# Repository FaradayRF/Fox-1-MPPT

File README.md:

# Fox-1-MPPT
This repository contains the Public Domain files of the [Radio Amateur Satellite Corporation](http://www.amsat.org) (AMSAT) Fox-1 satellite Maximum Power Point Tracker. This is a PCBA flying on the Fox-1 series of 1U cubesats which optimizes the power extracted from the six solar panels on the spacecraft using analog computing.

# Overview

The Fox-1 Maximum Power Point Tracker utilizes analog computing to track the solar panel voltage which generates the maximum amount of power from solar cells. It implements what is essentially a "temperature-based set-point constant voltage algorithm" MPPT. Since the solar cells are well-known, this design uses op-amps to compute the predicted voltage which will produce maximum power as fast as the analog bandwidth of the components used will allow it. Analog MPPT was chosen for it's "stateless" design due to radiation tolerance concerns of microcontrollers.

Revision 1.2 boards are Revision 1 PCB's with BOM modifications necessary for correct operation. This included stacking some capacitors ontop of feedback resistors in the RTD circuit for stability. Revision 1 PCB's are green soldermask in color. Revision 2 PCB's were created to adress these issues better and properly mount all parts with correct footprints and adress some other manufacturing needs. These boards are use a blue soldermask and the design files for the Rev 2.1 boards have been uploaded to this Github repository.

[READ THE FOX-1 MPPT TECHNICAL OVERVIEW TO UNDERSTAND THE PROJECT!](https://github.com/FaradayRF/Fox-1-MPPT/blob/master/Documents/Fox-1_MaximumPowerPointTracker.pdf)

# History
This project began as a [Rochester Institute of Technology](https://www.rit.edu/) Multi-disciplinary Senior Design (MSD) project during the 2012-2013 school year. Originally the [P13271 AMSAT-MPPT](http://edge.rit.edu/edge/P13271/public/Home) project which successfully delivered a proof-of-concept MPPT intended for a 3U cubesat, the design was continued and modified for use on the smaller Fox-1 satellites which are 1U in size.

## Original Team
The original RIT team to create this MPPT included
* Bryce Salmi, KB1LQC
* Brenton Salmi, KB1LQD
* Ian MacKenzi, KB3OCF
* Daniel Corriero

Work was performed over two years between 2013 and 2015 by Bryce Salmi and Brenton Salmi to bring the design to flight status from the P13271 project as seen here.

# Flights
The Revision 1.2 and Revision 2.1 Maximum Power Point Trackers are currently slated to fly on several launches to Low Earth Orbit with more launches being sought after. These flights are accurate as of 9/3/2016.

### Fox-1Cliff and Fox-1D
Two MPPTs will fly aboard two cubesats on the same launch. These satellites are Fox-1Cliff and Fox-1D which are being sent up on the Spaceflight SHERPA payload on a [SpaceX Falcon 9](http://www.spacex.com/falcon9).

### Fox-1B "RadFxSat"
One MPPT will be flying on the Fox-1B cubesat set to launch aboard a ULA [Delta II](http://www.ulalaunch.com/Products_DeltaII.aspx) rocket.

### Fox-1E "RadFxSat-2"
One MPPT will be flying on the Fox-1E cubesat set to launch aboard a [Virgin Galactic Launcher One](http://www.virgingalactic.com/satellite-launch/) in December, 2017.

# Project Structure
## Hardware Files
All hardware files are located in the [Hardware/Rev2_1](https://github.com/FaradayRF/Fox-1-MPPT/tree/master/Hardware/Rev2_1) directory. They consist of [Kicad EDA](http://kicad.org/) files which were developed using [Kicad Build: 2013-07-07 BZR 4022]https://downloads.kicad.org/kicad/windows/explore/stable) which is the July 2013 stable version of the EDA tool (Windows). Also placed into the hardware directory are the [project output files](https://github.com/FaradayRF/Fox-1-MPPT/tree/master/Hardware/Rev2_1/OutputFiles). These are the files which were used to order the PCBs and present an easy to use view of the design (PDF, Excel, Gerber, etc).

**Notable Documents**
* [MPPT Schematic PDF Export](https://github.com/FaradayRF/Fox-1-MPPT/blob/master/Hardware/Rev2_1/OutputFiles/TL1451_MPPT_Flight_Rev2_BW.pdf)
* [MPPT BOM](https://github.com/FaradayRF/Fox-1-MPPT/blob/master/Hardware/Rev2_1/OutputFiles/TL1451_MPPT_Flight_Rev2_BOM.xlsx)
* [MPPT Extra Components BOM](https://github.com/FaradayRF/Fox-1-MPPT/blob/master/Hardware/Rev2_1/OutputFiles/TL1451_MPPT_Flight_Rev2_Additional_BOM.xlsx)
 * Addition parts for the solar panels necessary for the MPPT to work
* [MPPT KiCad project file](https://github.com/FaradayRF/Fox-1-MPPT/blob/master/Hardware/Rev2_1/TL1451_MPPT_Flight_Rev1.pro)
* [KB1LQC KiCad schematic symbol library](https://github.com/FaradayRF/Fox-1-MPPT/blob/master/Hardware/Rev2_1/KB1LQC.lib)
* [KB1LQC KiCad PCBNew footprint library](https://github.com/FaradayRF/Fox-1-MPPT/blob/master/Hardware/Rev2_1/KB1LQC.mod)
* [MPPT PCB Fabrication Files](https://github.com/FaradayRF/Fox-1-MPPT/blob/master/Hardware/Rev2_1/OutputFiles/TL1451_MPPT_Flight_Rev2_1_FAB_Files.zip)
* [MPPT PCBA Assembly Files](https://github.com/FaradayRF/Fox-1-MPPT/blob/master/Hardware/Rev2_1/OutputFiles/TL1451_MPPT_Flight_Rev2_1_ASSEMBLY_Files.zip)

## Documents
The [documents folder](https://github.com/FaradayRF/Fox-1-MPPT/tree/master/Documents) contains support documents necessary to describe the design intentions and analysis of the MPPT.

**Notable Documents**
* [Fox-1 MPPT Technical Overview](https://github.com/FaradayRF/Fox-1-MPPT/blob/master/Documents/Fox-1_MaximumPowerPointTracker.pdf)
* [Fox-1 Satellite Solar Panel Calculations](https://github.com/FaradayRF/Fox-1-MPPT/blob/master/Documents/MPPT_Expected_Voltages_Fox-1.xlsx)
* [Fox-1 Solar Panel Telemetry Scaling](https://github.com/FaradayRF/Fox-1-MPPT/blob/master/Documents/PanelTemperatureScaling.xlsx)
 * Scaling telemetry downlinked from satellite over RF into Celcius from RTD circuit

## Images
The [images directory](https://github.com/FaradayRF/Fox-1-MPPT/tree/master/images) contains a select set of high-quality stock images showing the Rev 2 MPPT very clearly. Not much more needed to say about this :rocket:

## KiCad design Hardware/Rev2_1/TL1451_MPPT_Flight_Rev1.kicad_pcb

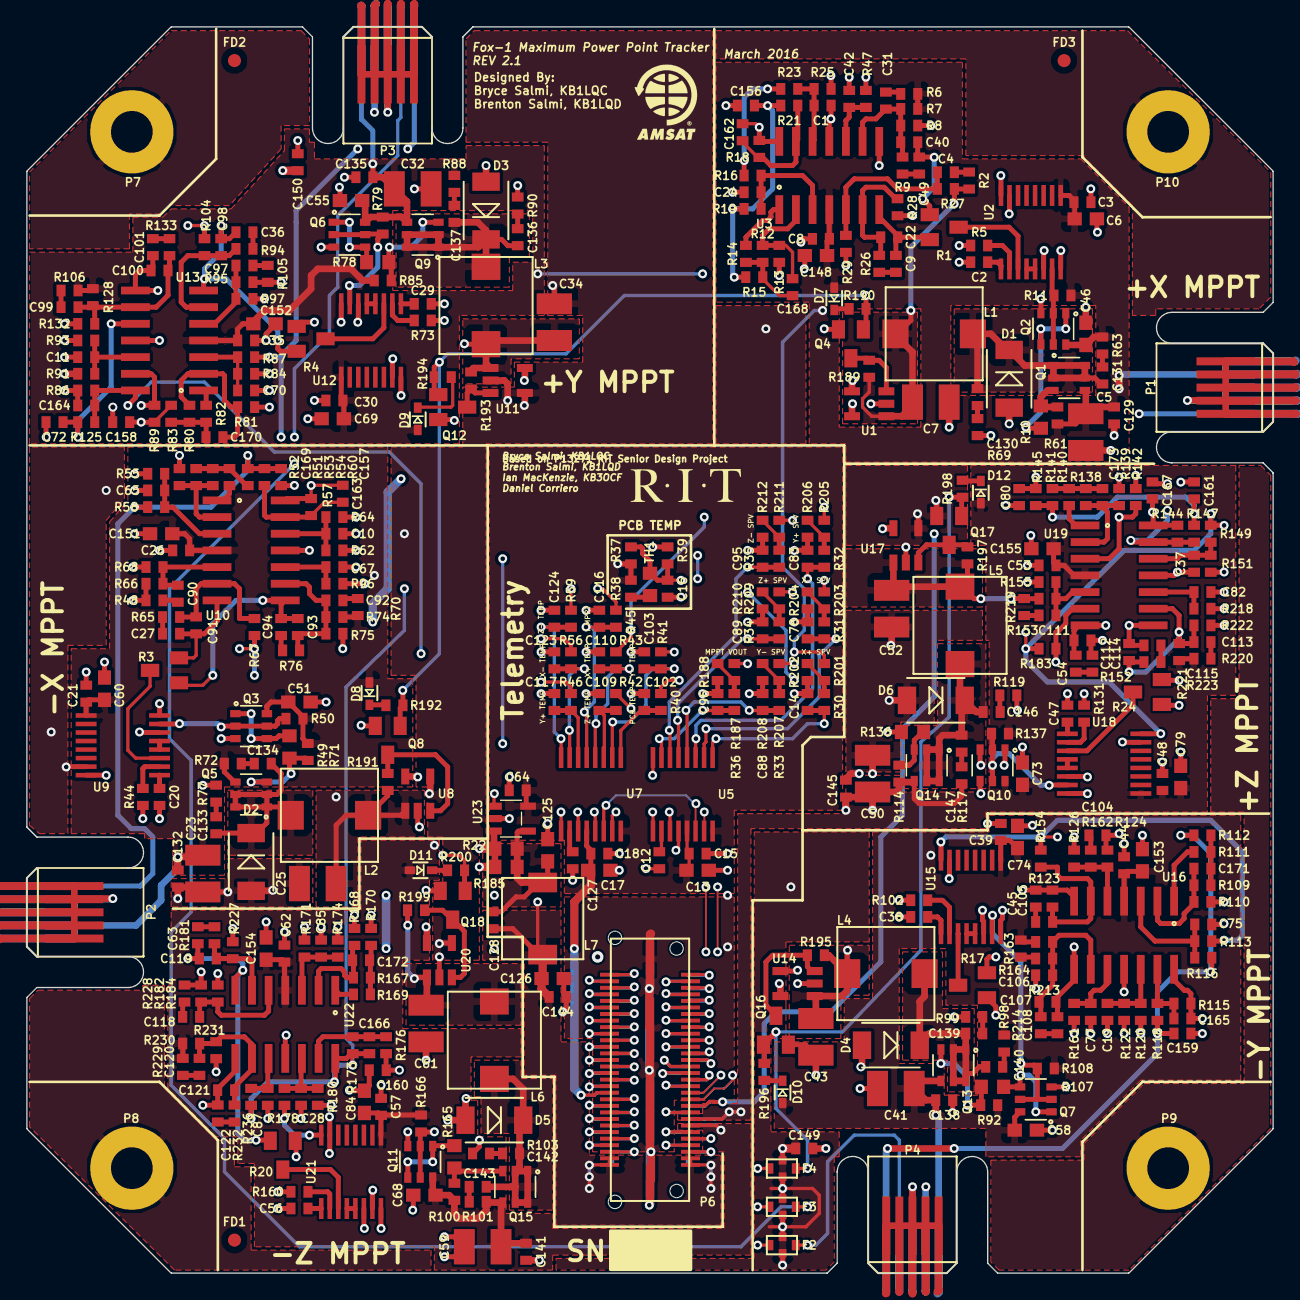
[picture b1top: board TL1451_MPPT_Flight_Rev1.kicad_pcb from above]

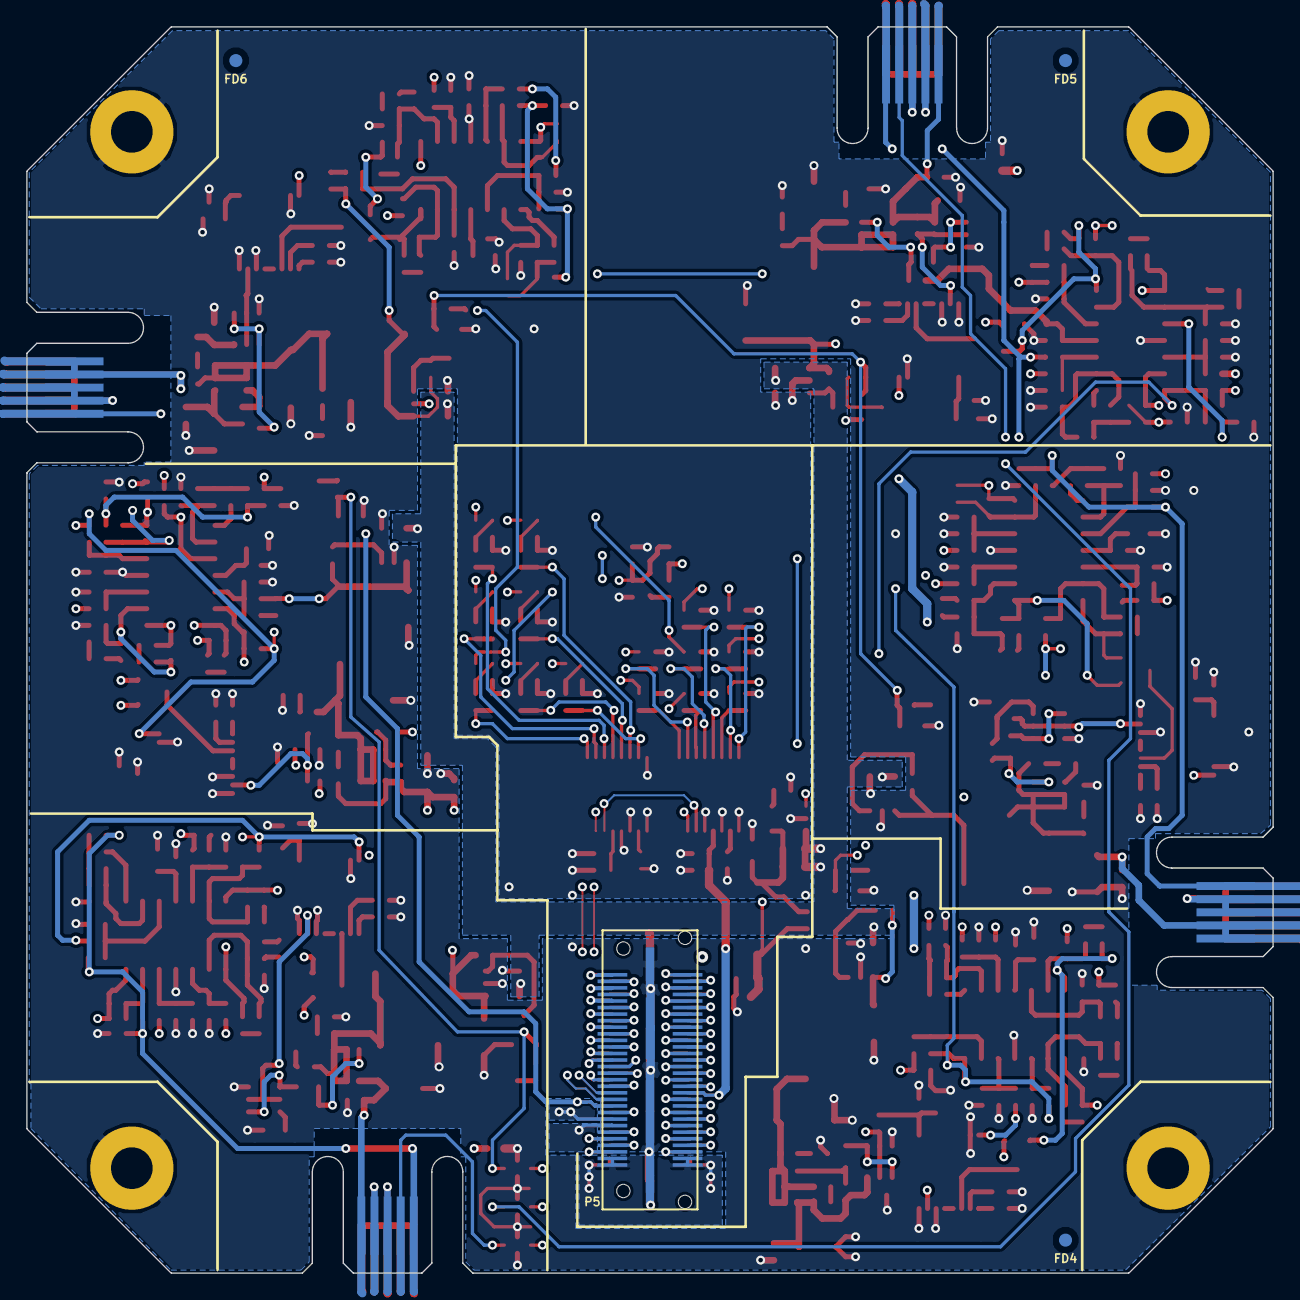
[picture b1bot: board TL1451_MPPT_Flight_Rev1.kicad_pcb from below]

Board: 4 copper layers, 95.0 x 95.0 mm, 455 parts (4 on the bottom side), 284 nets.

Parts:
C1, C3, C8, C10, C11, C15, C16, C18, C19, C21, C24, C26, C28, C30, C35, C37, C39, C44, C48, C53, C57, C62, C64, C65, C70, C75, C80, C85, C129, C132, C135, C138, C141, C144, C145, C149, C150, C156, C157, C158, C159, C160, C161, C162, C163, C164, C165, C166, C167, C168, C169, C170, C171, C172, C173: 0.1uF; C0402
C2, C20, C29, C38, C47, C56: 220pF; C0402
C4, C31, C90, C92, C97, C99, C104, C106, C111, C113, C118, C120: 0.012uF; C0402
C5, C7, C23, C25, C32, C34, C41, C43, C50, C52, C59, C61: 47uF; C1210
C6, C13, C17, C46, C51, C55, C58, C60, C68, C69, C73, C74, C79, C84, C148, C151, C152, C153, C154, C155: 1uF; C0603
C9, C27, C36, C45, C49, C54, C63, C94, C101, C108, C115, C122: 0.015uF; C0402
C12, C14, C42, C67, C72, C77, C78, C82, C83, C87, C88, C89, C95, C96, C102, C103, C109, C110, C116, C117, C123, C124, C127: 1uF; C0402
C22, C40, C91, C93, C98, C100, C105, C107, C112, C114, C119, C121: 820pF; C0402
C125, C126: 0.39uF; C0603
C128: 0.01uF; C0402
C130, C131, C133, C134, C136, C137, C139, C140, C142, C143, C146, C147: DNP; C0402
D1, D2, D3, D4, D5, D6: PMEG3020EP; SOD128
D7, D8, D9, D10, D11, D12: SDM10U45-7; SOD523
F2, F3, F4: NFL21SP106X1C3D; NFL21SP
FD1, FD2, FD3, FD4, FD5, FD6: FIDUCIAL; FD1
G1: AMSAT_LOGO_SMALL; AMSAT_Logo_Small
G2: RIT_LOGO_SMALL; RIT_Logo_Small
L1, L2, L3, L4, L5, L6: 22uH; CLF7045T
L7: 10uH; SLF6045
P1, P2, P3, P4: CONN_5X2; MEC1-105-02-L-D-NP-A
P5: QSH-030-01-X-D-A; QSH-030-01-L-D-A
P6: QTH-030-02-X-D-A; QTH-030-02-L-D-A
P7, P8, P9, P10: CONN_1; FOX_Mounting_Hole
Q1, Q5, Q9, Q13, Q14, Q15: DMP2066LDM-7; SOT26
Q2, Q3, Q6, Q7, Q10, Q11: MMDT2227M; SOT26
Q4, Q8, Q12, Q16, Q17, Q18: 2N7002K; SOT23
R1, R3, R4, R17, R20, R24: MPMT4001AT1; SOT23
R2, R6, R48, R70, R105, R106, R162, R163, R219, R220, R228, R229: 261; R0402
R5, R44, R73, R102, R131, R160: 4.99K; R0402
R7, R27, R66, R74, R95, R124, R128, R153, R164, R182, R221, R230: 4.75K; R0402
R8, R75, R132, R213, R222, R231: 1.54K; R0402
R9, R21, R26, R60, R65, R76, R89, R94, R118, R123, R133, R147, R152, R176, R181, R214, R223, R232: 3.32K; R0402
R10, R49, R78, R107, R136, R165: 6.04; R0603
R11, R50, R79, R108, R137, R166: 2K; R0402
R12, R13, R16, R19, R51, R52, R55, R58, R80, R81, R84, R87, R109, R110, R113, R116, R138, R139, R142, R145, R167, R168, R171, R174: 249K; R0402
R14, R53, R82, R111, R140, R169: 100; R0402
R15, R54, R83, R112, R141, R170: 2.49K; R0402
R18, R57, R86, R115, R144, R173: 27K; R0402
R22, R185: 0.051; R0603
R23, R62, R91, R120, R149, R178: 24.3K; R0402
R25, R64, R93, R122, R151, R180: 2.4K; R0402
R28, R30, R31, R32, R33, R34, R35, R36, R40, R41, R42, R43, R45, R46, R56, R59, R67, R104, R154, R183, R189, R190, R191, R192, R193, R194, R195, R196, R197, R198, R199, R200, R227: 10K; R0402
R29, R68, R97, R126, R155, R184: 6.49K; R0402
R37: 71.5K; R0402
R38: 330; R0402
R39: 9.09K; R0402
R47, R96, R125, R161, R218, R236: 47K; R0402
R61, R71, R85, R92, R100, R114: 205K; R0402
R63, R69, R72, R77, R88, R90, R98, R99, R101, R103, R117, R119: DNP; R0402
R187, R202, R204, R206, R208, R210, R212: 30.1K; R0402
R188: 40.2K; R0402
R201, R203, R205, R207, R209, R211: 51.1K; R0402
TH1: NTCS0603E3103FMT; R0603
U1, U8, U11, U14, U17, U20: LTC4411; TSOT23-5
U2, U9, U12, U15, U18, U21: TL1451A; PW16
U3, U10, U13, U16, U19, U22: LM6144A; SO14
U5, U7: ADS7828; PW16
U23: INA195; SOT23-5

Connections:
/ADC Channels/Temperature & Current ADC/I2C_SCL: P5.37, P6.37, U5.14, U7.14
/ADC Channels/Temperature & Current ADC/I2C_SDA: P5.39, P6.39, U5.15, U7.15
/ADC Channels/Temperature & Current ADC/MPPT-OUTPUT-CURRENT: R45.1, U23.1
/ADC Channels/Temperature & Current ADC/SENSOR_POWER: C13.1, C15.1, C17.1, C18.1, C64.1, P5.38, P6.38, R37.1, R38.1, U5.13, U5.16, U7.12, U7.16, U23.5
/ADC Channels/Voltage Sense ADC/VMPPT: R36.1, R187.2, R188.1
/BUS44: C149.1, P4.8, P5.44, P6.44
/BUS46: F2.3, P4.4
/BUS48: F3.3, P3.4
/BUS50: C150.1, P3.8, P5.50, P6.50
/Connectors/BUS1: P5.1, P6.1
/Connectors/BUS2: P5.2, P6.2
/Connectors/BUS3: P5.3, P6.3
/Connectors/BUS4: P5.4, P6.4
/Connectors/BUS5: P5.5, P6.5
/Connectors/BUS6: P5.6, P6.6
/Connectors/BUS7: P5.7, P6.7
/Connectors/BUS8: P5.8, P6.8
/Connectors/BUS9: P5.9, P6.9
/Connectors/BUS10: P5.10, P6.10
/Connectors/BUS11: P5.11, P6.11
/Connectors/BUS12: P5.12, P6.12
/Connectors/BUS13: P5.13, P6.13
/Connectors/BUS14: P5.14, P6.14
/Connectors/BUS15: P5.15, P6.15
/Connectors/BUS16: P5.16, P6.16
/Connectors/BUS17: P5.17, P6.17
/Connectors/BUS18: P5.18, P6.18
/Connectors/BUS19: P5.19, P6.19
/Connectors/BUS20: P5.20, P6.20
/Connectors/BUS21: P5.21, P6.21
/Connectors/BUS22: P5.22, P6.22
/Connectors/BUS23: P5.23, P6.23
/Connectors/BUS24: P5.24, P6.24
/Connectors/BUS25: P5.25, P6.25
/Connectors/BUS26: P5.26, P6.26
/Connectors/BUS27: P5.27, P6.27
/Connectors/BUS28: P5.28, P6.28
/Connectors/BUS29-UNF: F4.1, P5.29, P6.29
/Connectors/BUS30: P5.30, P6.30
/Connectors/BUS31: P5.31, P6.31
/Connectors/BUS32: P5.32, P6.32
/Connectors/BUS33: P5.33, P6.33
/Connectors/BUS34: P5.34, P6.34
/Connectors/BUS35: P5.35, P6.35
/Connectors/BUS36: P5.36, P6.36
/Connectors/BUS40: P5.40, P6.40
/Connectors/BUS42: P5.42, P6.42
/Connectors/BUS46-UNF: F2.1, P5.46, P6.46
/Connectors/BUS48-UNF: F3.1, P5.48, P6.48
/Connectors/BUS49: P5.49, P6.49
/Connectors/BUS51: P5.51, P6.51
/Connectors/BUS52: P5.52, P6.52
/Connectors/BUS53: P5.53, P6.53
/Connectors/BUS54: P5.54, P6.54
/Connectors/BUS55: P5.55, P6.55
/Connectors/BUS56: P5.56, P6.56
/Current Sense/I_SENSE+: R22.1, R185.1, U1.5, U8.5, U11.5, U14.5, U17.5, U20.5, U23.3
/Current Sense/Sense-: C125.1, C128.1, L7.1, R22.2, R185.2, U23.4
/Current Sense/VBATT: C126.1, C128.2, C144.1, L7.2, P5.57, P5.58, P5.59, P5.60, P6.57, P6.58, P6.59, P6.60, R187.1
/MPPT_String_X+/Amplifiers/VREF: R16.1, R23.1, R28.1, U2.16
/MPPT_String_X+/Amplifiers/Verror: R1.3, U2.3
/MPPT_String_X+/RTD+: C156.2, P1.2, R15.2, R19.2, R21.1
/MPPT_String_X+/TL1451 Control/MOSFET Driver/GATE-DRIVE: Q2.1, Q2.4, R10.1
/MPPT_String_X+/TL1451 Control/MOSFET Driver/PWM-IN: Q2.2, Q2.5, R11.2, U2.7
/MPPT_String_X+/TL1451 Control/MPPT-OUT: C7.1, L1.2, R2.1, R27.1, R189.1, U1.1
/MPPT_String_X+/TL1451 Control/Non-Synchronouse_BUCK/Vswitch: C130.1, C131.2, D1.1, L1.1, Q1.1, Q1.2, Q1.5, Q1.6
/MPPT_String_X+/Vpanel+: C3.1, C5.1, C6.1, C8.1, C46.1, C129.1, C148.1, D7.2, P1.8, P1.10, Q1.4, Q2.6, R6.1, R7.1, R11.1, R61.1, R63.1, R201.1, U2.9, U3.4
/MPPT_String_X+/Vtemp: C162.1, R18.2, R43.1, R47.1, U3.14
/MPPT_String_X+/~SolarSafe~: F4.3, Q4.1, Q8.1, Q12.1, Q16.1, Q17.1, Q18.1, R190.2, R192.2, R194.2, R196.2, R198.2, R200.2
/MPPT_String_X-/Amplifiers/VREF: R55.1, R62.1, R67.1, U9.16
/MPPT_String_X-/Amplifiers/Verror: R3.3, U9.3
/MPPT_String_X-/RTD+: C157.2, P2.2, R54.2, R58.2, R60.1
/MPPT_String_X-/TL1451 Control/MOSFET Driver/GATE-DRIVE: Q3.1, Q3.4, R49.1
/MPPT_String_X-/TL1451 Control/MOSFET Driver/PWM-IN: Q3.2, Q3.5, R50.2, U9.7
/MPPT_String_X-/TL1451 Control/MPPT-OUT: C25.1, L2.2, R48.1, R66.1, R191.1, U8.1
/MPPT_String_X-/TL1451 Control/Non-Synchronouse_BUCK/Vswitch: C133.1, C134.2, D2.1, L2.1, Q5.1, Q5.2, Q5.5, Q5.6
/MPPT_String_X-/Vpanel+: C21.1, C23.1, C26.1, C51.1, C60.1, C132.1, C151.1, D8.2, P2.8, P2.10, Q3.6, Q5.4, R50.1, R70.1, R71.1, R72.1, R74.1, R203.1, U9.9, U10.4
/MPPT_String_X-/Vtemp: C163.1, R56.1, R57.2, R96.1, U10.14
/MPPT_String_Y+/Amplifiers/VREF: R84.1, R91.1, R104.1, U12.16
/MPPT_String_Y+/Amplifiers/Verror: R4.3, U12.3
/MPPT_String_Y+/RTD+: C158.2, P3.2, R83.2, R87.2, R89.1
/MPPT_String_Y+/TL1451 Control/MOSFET Driver/GATE-DRIVE: Q6.1, Q6.4, R78.1
/MPPT_String_Y+/TL1451 Control/MOSFET Driver/PWM-IN: Q6.2, Q6.5, R79.2, U12.7
/MPPT_String_Y+/TL1451 Control/MPPT-OUT: C34.1, L3.2, R95.1, R105.1, R193.1, U11.1
/MPPT_String_Y+/TL1451 Control/Non-Synchronouse_BUCK/Vswitch: C136.1, C137.2, D3.1, L3.1, Q9.1, Q9.2, Q9.5, Q9.6
/MPPT_String_Y+/Vpanel+: C30.1, C32.1, C35.1, C55.1, C69.1, C135.1, C152.1, D9.2, P3.10, Q6.6, Q9.4, R79.1, R85.1, R88.1, R106.1, R128.1, R205.1, U12.9, U13.4
/MPPT_String_Y+/Vtemp: C164.1, R46.1, R86.2, R125.1, U13.14
/MPPT_String_Y-/Amplifiers/VREF: R113.1, R120.1, R154.1, U15.16
/MPPT_String_Y-/Amplifiers/Verror: R17.3, U15.3
/MPPT_String_Y-/RTD+: C159.2, P4.2, R112.2, R116.2, R118.1
/MPPT_String_Y-/TL1451 Control/MOSFET Driver/GATE-DRIVE: Q7.1, Q7.4, R107.1
/MPPT_String_Y-/TL1451 Control/MOSFET Driver/PWM-IN: Q7.2, Q7.5, R108.2, U15.7
/MPPT_String_Y-/TL1451 Control/MPPT-OUT: C43.1, L4.2, R124.1, R162.1, R195.1, U14.1
/MPPT_String_Y-/TL1451 Control/Non-Synchronouse_BUCK/Vswitch: C139.1, C140.2, D4.1, L4.1, Q13.1, Q13.2, Q13.5, Q13.6
/MPPT_String_Y-/Vpanel+: C39.1, C41.1, C44.1, C58.1, C74.1, C138.1, C153.1, D10.2, P4.10, Q7.6, Q13.4, R92.1, R98.1, R108.1, R163.1, R164.1, R207.1, U15.9, U16.4
/MPPT_String_Y-/Vtemp: C165.1, R41.1, R115.2, R161.1, U16.14
/MPPT_String_Z+/Amplifiers/VREF: R142.1, R149.1, R183.1, U18.16
/MPPT_String_Z+/Amplifiers/Verror: R24.3, U18.3
/MPPT_String_Z+/RTD+: C161.2, P5.41, P6.41, R141.2, R145.2, R147.1
/MPPT_String_Z+/TL1451 Control/MOSFET Driver/GATE-DRIVE: Q10.1, Q10.4, R136.1
/MPPT_String_Z+/TL1451 Control/MOSFET Driver/PWM-IN: Q10.2, Q10.5, R137.2, U18.7
/MPPT_String_Z+/TL1451 Control/MPPT-OUT: C52.1, L5.2, R153.1, R197.1, R219.1, U17.1
/MPPT_String_Z+/TL1451 Control/Non-Synchronouse_BUCK/Vswitch: C146.1, C147.2, D6.1, L5.1, Q14.1, Q14.2, Q14.5, Q14.6
/MPPT_String_Z+/Vpanel+: C48.1, C50.1, C53.1, C73.1, C79.1, C145.1, C155.1, D12.2, P5.45, P6.45, Q10.6, Q14.4, R114.1, R117.1, R137.1, R209.1, R220.1, R221.1, U18.9, U19.4
/MPPT_String_Z+/Vtemp: C167.1, R42.1, R144.2, R218.1, U19.14
/MPPT_String_Z-/Amplifiers/VREF: R171.1, R178.1, R227.1, U21.16
/MPPT_String_Z-/Amplifiers/Verror: R20.3, U21.3
/MPPT_String_Z-/RTD+: C160.2, P5.43, P6.43, R170.2, R174.2, R176.1
/MPPT_String_Z-/TL1451 Control/MOSFET Driver/GATE-DRIVE: Q11.1, Q11.4, R165.1
/MPPT_String_Z-/TL1451 Control/MOSFET Driver/PWM-IN: Q11.2, Q11.5, R166.2, U21.7
/MPPT_String_Z-/TL1451 Control/MPPT-OUT: C61.1, L6.2, R182.1, R199.1, R228.1, U20.1
/MPPT_String_Z-/TL1451 Control/Non-Synchronouse_BUCK/Vswitch: C142.1, C143.2, D5.1, L6.1, Q15.1, Q15.2, Q15.5, Q15.6
/MPPT_String_Z-/Vpanel+: C57.1, C59.1, C62.1, C68.1, C84.1, C141.1, C154.1, D11.2, P5.47, P6.47, Q11.6, Q15.4, R100.1, R101.1, R166.1, R211.1, R229.1, R230.1, U21.9, U22.4
/MPPT_String_Z-/Vtemp: C166.1, R59.1, R173.2, R236.1, U22.14
/Panel Voltage Scaling/Vsense+X: R30.1, R201.2, R202.1
/Panel Voltage Scaling/Vsense+Y: R32.1, R205.2, R206.1
/Panel Voltage Scaling/Vsense+Z: R34.1, R209.2, R210.1
/Panel Voltage Scaling/Vsense-X: R31.1, R203.2, R204.1
/Panel Voltage Scaling/Vsense-Y: R33.1, R207.2, R208.1
/Panel Voltage Scaling/Vsense-Z: R35.1, R211.2, R212.1
GND: C1.1, C2.2, C3.2, C5.2, C6.2, C7.2, C8.2, C10.1, C11.1, C12.2, C13.2, C14.2, C15.2, C16.2, C17.2, C18.2, C19.1, C20.2, C21.2, C23.2, C24.1, C25.2, C26.2, C28.1, C29.2, C30.2, C32.2, C34.2, C35.2, C37.1, C38.2, C39.2, C41.2, C42.1, C43.2, C44.2, C46.2, C47.2, C48.2, C50.2, C51.2, C52.2, C53.2, C55.2, C56.2, C57.2, C58.2, C59.2, C60.2, C61.2, C62.2, C64.2, C65.1, C67.1, C68.2, C69.2, C70.1, C72.1, C73.2, C74.2, C75.1, C77.1, C78.2, C79.2, C80.1, C82.1, C83.2, C84.2, C85.1, C87.1, C88.2, C89.2, C95.2, C96.2, C102.2, C103.2, C109.2, C110.2, C116.2, C117.2, C123.2, C124.2, C125.2, C126.2, C127.2, C129.2, C132.2, C135.2, C138.2, C141.2, C144.2, C145.2, C148.2, C149.2, C150.2, C151.2, C152.2, C153.2, C154.2, C155.2, C156.1, C157.1, C158.1, C159.1, C160.1, C161.1, D1.2, D2.2, D3.2, D4.2, D5.2, D6.2, F2.2, F3.2, F4.2, P1.1, P1.3, P1.4, P1.5, P1.6, P1.7, P1.9, P2.1, P2.3, P2.4, P2.5, P2.6, P2.7, P2.9, P3.1, P3.3, P3.5, P3.6, P3.7, P3.9, P4.1, P4.3, P4.5, P4.6, P4.7, P4.9, P5.61, P5.62, P5.63, P5.64, P6.61, P6.62, P6.63, P6.64, P7.1, P8.1, P9.1, P10.1, Q2.3, Q3.3, Q4.2, Q6.3, Q7.3, Q8.2, Q10.3, Q11.3, Q12.2, Q16.2, Q17.2, Q18.2, R5.2, R8.2, R13.1, R25.2, R29.2, R39.2, R44.2, R52.1, R64.2, R68.2, R69.2, R73.2, R75.2, R77.2, R81.1, R90.2, R93.2, R97.2, R99.2, R102.2, R103.2, R110.1, R119.2, R122.2, R126.2, R131.2, R132.2, R139.1, R151.2, R155.2, R160.2, R168.1, R180.2, R184.2, R188.2, R202.2, R204.2, R206.2, R208.2, R210.2, R212.2, R213.2, R222.2, R231.2, U1.2, U1.4, U2.6, U2.8, U2.15, U3.11, U5.8, U5.9, U5.11, U5.12, U7.9, U7.11, U7.13, U8.2, U8.4, U9.6, U9.8, U9.15, U10.11, U11.2, U11.4, U12.6, U12.8, U12.15, U13.11, U14.2, U14.4, U15.6, U15.8, U15.15, U16.11, U17.2, U17.4, U18.6, U18.8, U18.15, U19.11, U20.2, U20.4, U21.6, U21.8, U21.15, U22.11, U23.2
unnamed: Q4.3, R189.2, U1.3
unnamed: D7.1, R190.1
unnamed: D8.1, R192.1
unnamed: Q8.3, R191.2, U8.3
unnamed: D9.1, R194.1
unnamed: Q12.3, R193.2, U11.3
unnamed: D10.1, R196.1
unnamed: Q16.3, R195.2, U14.3
unnamed: Q17.3, R197.2, U17.3
unnamed: D12.1, R198.1
unnamed: Q18.3, R199.2, U20.3
unnamed: D11.1, R200.1
unnamed: U2.4, U2.5
unnamed: R5.1, U2.2
unnamed: C2.1, U2.1
unnamed: C1.2, R23.2, R25.1, U3.12
unnamed: C31.2, C40.1, R7.2, R8.1, R9.1, U3.9
unnamed: C168.1, R12.1, R13.2, U3.2
unnamed: C168.2, R12.2, R14.2, R15.1
unnamed: R14.1, U3.1
unnamed: C49.1, R9.2
unnamed: C4.1, R2.2
unnamed: C31.1, R6.2
unnamed: C9.1, R26.2
unnamed: C22.1, R26.1, R28.2, U3.6
unnamed: C4.2, R27.2, R29.1, U3.5
unnamed: C42.2, R47.2, U3.10
unnamed: C40.2, C49.2, R1.1, U3.8
unnamed: C9.2, C22.2, R1.2, U3.7
unnamed: C24.2, R16.2, R19.1, U3.3
unnamed: C162.2, R18.1, R21.2, U3.13
unnamed: C96.1, R36.2, U5.7
unnamed: C12.1, U5.10
unnamed: C95.1, R35.2, U5.6
unnamed: C14.1, R30.2, U5.1
unnamed: C89.1, R34.2, U5.5
unnamed: C88.1, R33.2, U5.4
unnamed: C83.1, R32.2, U5.3
unnamed: C78.1, R31.2, U5.2
unnamed: C116.1, R45.2, U7.5
unnamed: C110.1, R43.2, U7.4
unnamed: C109.1, R42.2, U7.3
unnamed: C103.1, R41.2, U7.2
unnamed: R38.2, TH1.1
unnamed: C124.1, R59.2, U7.8
unnamed: C123.1, R56.2, U7.7
unnamed: C127.1, U7.10
unnamed: C102.1, R40.2, U7.1
unnamed: C117.1, R46.2, U7.6
unnamed: C16.1, R37.2, R39.1, R40.1, TH1.2
unnamed: U9.4, U9.5
unnamed: R44.1, U9.2
unnamed: C20.1, U9.1
unnamed: C67.2, R96.2, U10.10
unnamed: C163.2, R57.1, R60.2, U10.13
unnamed: C27.2, C91.2, R3.2, U10.7
unnamed: C27.1, R65.2
unnamed: C93.2, C94.2, R3.1, U10.8
unnamed: C94.1, R76.2
unnamed: C92.2, C93.1, R74.2, R75.1, R76.1, U10.9
unnamed: C92.1, R70.2
unnamed: C90.2, R66.2, R68.1, U10.5
unnamed: C90.1, R48.2
unnamed: C10.2, R62.2, R64.1, U10.12
unnamed: C91.1, R65.1, R67.2, U10.6
unnamed: C65.2, R55.2, R58.1, U10.3
unnamed: C169.1, R51.1, R52.2, U10.2
unnamed: R53.1, U10.1
unnamed: C169.2, R51.2, R53.2, R54.1
unnamed: C29.1, U12.1
unnamed: R73.1, U12.2
unnamed: U12.4, U12.5
unnamed: C72.2, R125.2, U13.10
unnamed: C99.1, R106.2
unnamed: C97.1, R105.2
unnamed: C97.2, R95.2, R97.1, U13.5
unnamed: C98.1, R94.1, R104.2, U13.6
unnamed: C36.1, R94.2
unnamed: C99.2, C100.1, R128.2, R132.1, R133.1, U13.9
unnamed: C101.1, R133.2
unnamed: C170.2, R80.2, R82.2, R83.1
unnamed: C100.2, C101.2, R4.1, U13.8
unnamed: C70.2, R84.2, R87.1, U13.3
unnamed: C170.1, R80.1, R81.2, U13.2
unnamed: R82.1, U13.1
unnamed: C36.2, C98.2, R4.2, U13.7
unnamed: C164.2, R86.1, R89.2, U13.13
unnamed: C11.2, R91.2, R93.1, U13.12
unnamed: U15.4, U15.5
unnamed: R102.1, U15.2
unnamed: C38.1, U15.1
unnamed: C165.2, R115.1, R118.2, U16.13
unnamed: C45.1, R123.2
unnamed: C108.1, R214.2
unnamed: C105.1, R123.1, R154.2, U16.6
unnamed: C104.1, R162.2
unnamed: R111.1, U16.1
unnamed: C171.2, R109.2, R111.2, R112.1
unnamed: C171.1, R109.1, R110.2, U16.2
unnamed: C75.2, R113.2, R116.1, U16.3
unnamed: C77.2, R161.2, U16.10
unnamed: C107.2, C108.2, R17.1, U16.8
unnamed: C106.2, C107.1, R164.2, R213.1, R214.1, U16.9
unnamed: C45.2, C105.2, R17.2, U16.7
unnamed: C106.1, R163.2
unnamed: C104.2, R124.2, R126.1, U16.5
unnamed: C19.2, R120.2, R122.1, U16.12
unnamed: U18.4, U18.5
unnamed: R131.1, U18.2
unnamed: C47.1, U18.1
unnamed: C112.1, R152.1, R183.2, U19.6
unnamed: C54.1, R152.2
unnamed: C111.2, R153.2, R155.1, U19.5
unnamed: C115.1, R223.2
unnamed: C111.1, R219.2
unnamed: R140.1, U19.1
unnamed: C37.2, R149.2, R151.1, U19.12
unnamed: C54.2, C112.2, R24.2, U19.7
unnamed: C113.1, R220.2
unnamed: C80.2, R142.2, R145.1, U19.3
unnamed: C173.1, R138.1, R139.2, U19.2
unnamed: C173.2, R138.2, R140.2, R141.1
unnamed: C114.2, C115.2, R24.1, U19.8
unnamed: C82.2, R218.2, U19.10
unnamed: C113.2, C114.1, R221.2, R222.1, R223.1, U19.9
unnamed: C167.2, R144.1, R147.2, U19.13
unnamed: C56.1, U21.1
unnamed: R160.1, U21.2
unnamed: U21.4, U21.5
unnamed: C118.2, R182.2, R184.1, U22.5
unnamed: C63.2, C119.2, R20.2, U22.7
unnamed: C63.1, R181.2
unnamed: C119.1, R181.1, R227.2, U22.6
unnamed: C122.1, R232.2
unnamed: C120.2, C121.1, R230.2, R231.1, R232.1, U22.9
unnamed: C120.1, R229.2
unnamed: C87.2, R236.2, U22.10
unnamed: C121.2, C122.2, R20.1, U22.8
unnamed: C118.1, R228.2
unnamed: C172.2, R167.2, R169.2, R170.1
unnamed: C172.1, R167.1, R168.2, U22.2
unnamed: R169.1, U22.1
unnamed: C166.2, R173.1, R176.2, U22.13
unnamed: C85.2, R171.2, R174.1, U22.3
unnamed: C28.2, R178.2, R180.1, U22.12
unnamed: C130.2, R69.1
unnamed: C131.1, R63.2
unnamed: Q1.3, R10.2, R61.2
unnamed: C134.1, R72.2
unnamed: C133.2, R77.1
unnamed: Q5.3, R49.2, R71.2
unnamed: C137.1, R88.2
unnamed: Q9.3, R78.2, R85.2
unnamed: C136.2, R90.1
unnamed: C140.1, R98.2
unnamed: C139.2, R99.1
unnamed: Q13.3, R92.2, R107.2
unnamed: C146.2, R119.1
unnamed: Q14.3, R114.2, R136.2
unnamed: C147.1, R117.2
unnamed: C142.2, R103.1
unnamed: C143.1, R101.2
unnamed: Q15.3, R100.2, R165.2

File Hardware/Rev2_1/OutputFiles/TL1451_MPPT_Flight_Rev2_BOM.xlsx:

The Radio Amateur Satelite Corporation - AMSAT
Fox-1 Maximum Power Point Tracker
Revision | 2 | Engineer | Bryce Salmi |  | Part Count | 421
Date | 42339 |  | KB1LQC |  | Line Items | 52
Reference Designator | Value | Quantity | Footprint | Tolerance/Rating | Manufacturer Part Number | Supplier Link
C12 C14 C78 C83 C42 C67 C72 C77 C82 C87 C88 C89 C95 C96 C102 C103 C109 C110 C11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 | 1uF | 23 | C0402 | 16V | GRM155C81E105ME11D | http://www.digikey.com/product-search/en?pv252=42&FV=ffec150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
C125 C126 | 0.39uF | 2 | C0603 | 16V | GRM188R71C394KA88D | http://www.digikey.com/product-search/en?pv13=45&FV=ffec150e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
C128 | 0.01uF | 1 | C0402 | 16V | GRM155R71C103KA01D | http://www.digikey.com/product-detail/en/GRM155R71C103KA01D/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
C13 C17 C46 C51 C55 C58 C68 C73 C6 C60 C69 C74 C79 C84 C148 C151 C152 C153 C154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 | 1uF | 20 | C0603 | 16V | GRM188R7YA105KA12D | http://www.digikey.com/product-detail/en/GRM188R7YA105KA12D/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
C15 C16 C18 C1 C10 C11 C19 C28 C37 C3 C21 C30 C39 C48 C57 C8 C26 C35 C44 C53 C6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 | 0.1uF | 55 | C0402 | 16V | GRM155R71C104KA88D | http://www.digikey.com/product-detail/en/GRM155R71C104KA88D/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
C2 C20 C29 C38 C47 C56 | 220pF | 6 | C0402 | 16V, NPO/C0G | GRM1555C1H221FA01D | https://www.digikey.com/product-detail/en/GRM1555C1H221FA01D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
C22 C91 C98 C105 C112 C119 C40 C93 C100 C107 C114 C121 | 820pF | 12 | C0402 | 50V | GRM155R71H821KA01D | http://www.digikey.com/product-detail/en/GRM155R71H821KA01D/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
C130 C133 C136 C139 C142 C146 C131 C134 C137 C140 C143 C147 | DNP | 12 | C0402 | 16V | DNP
C4 C90 C97 C104 C111 C118 C31 C92 C99 C106 C113 C120 | 0.012uF | 12 | C0402 | 16V | GRM155R71C123KA01D | http://www.digikey.com/product-detail/en/GRM155R71C123KA01D/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
C42 C67 C72 C77 C82 C87 | 1uF | 6 | C0402 | 35V | C1005X5R1V105K050BC | https://www.digikey.com/product-detail/en/C1005X5R1V105K050B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
C5 C23 C32 C41 C50 C59 C7 C25 C34 C43 C52 C61 | 47uF | 12 | C1210 | 16V | GRM32ER61C476KE15K | http://www.digikey.com/product-search/en?pv3=3&pv14=9&FV=ffe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
C9 C27 C36 C45 C54 C63 C49 C94 C101 C108 C115 C122 | 0.015uF | 12 | C0402 | 16V | GRM155R71C153KA01D | http://www.digikey.com/product-detail/en/GRM155R71C153KA01D/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
D1 D2 D3 D4 D5 D6 | PMEG3020EP | 6 | SOD128 |  | PMEG3020EP,115 | http://www.digikey.com/product-detail/en/PMEG3020EP,115/568-7402-1-ND/2697503
D7 D9 D11 D13 D15 D17 | SDM10U45-7 | 6 | SOD523 |  | SDM10U45-7 | http://www.digikey.com/product-search/en?pv7=2&k=SDM10U45-7&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
R1 R3 R4 R17 R20 R24 | MPMT4001AT1 | 6 | SOT23 |  | MPMT4001AT1 | https://www.digikey.com/product-search/en?pv7=2&k=MPMT4001AT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
F2 F3 F4 | NFL21SP106X1C3D | 3 | NFL21SP |  | NFL21SP106X1C3D | http://www.digikey.com/product-detail/en/NFL21SP106X1C3D/490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
G1 | AMSAT_LOGO_SMALL | 1 | AMSAT_Logo_Small |  | DNP
G2 | RIT_LOGO_SMALL | 1 | RIT_Logo_Small |  | DNP
L1 L2 L3 L4 L5 L6 | 22uH | 6 | CLF7045T | CLF7045T-220M-H | CLF7045T-220M-H | http://www.digikey.com/product-search/en?pv7=2&k=CLF7045T-22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
L7 | 10uH | 1 | SLF6045 | SLF6045T-100M1R6-3PF | SLF6045T-100M1R6-3PF | http://www.digikey.com/product-search/en?pv7=2&FV=4c000a&k=S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
P1 P2 P3 P4 | CONN_5X2 | 4 | MEC1-105-02-L-D-NP-A |  | DNP
P5 | QSH-030-01-X-D-A | 1 | QSH-030-01-L-D-A |  | QSH-030-01-L-D-A | http://www.digikey.com/product-detail/en/QSH-030-01-L-D-A/SA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
P6 | QTH-030-02-X-D-A | 1 | QTH-030-02-L-D-A |  | QTH-030-02-L-D-A | http://www.digikey.com/product-detail/en/QTH-030-02-L-D-A/SA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
P7 P8 P9 P10 | CONN_1 | 4 | FOX_Mounting_Hole |  | DNP
Q1 Q5 Q9 Q13 Q14 Q15 | DMP2066LDM-7 | 6 | SOT26 |  | DMP2066LDM-7 | http://www.digikey.com/product-search/en?pv7=2&k=DMP2066LDM-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
Q2 Q3 Q6 Q7 Q10 Q11 | MMDT2227M | 6 | SOT26 |  | MMDT2227M-7 | http://www.digikey.com/product-detail/en/MMDT2227M-7/MMDT222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
Q4 Q8 Q12 Q16 Q17 Q18 | 2N7002K | 6 | SOT23 |  | 2N7002K | http://www.digikey.com/product-detail/en/2N7002K/2N7002KCT-N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
R10 R49 R78 R107 R136 R165 | 6.04 | 6 | R0603 | 0.01 | CRCW06036R04FKEA | http://www.digikey.com/product-search/en?s=18616&pv17=103&FV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
R11 R50 R79 R108 R137 R166 | 2K | 6 | R0402 | 1E-3 | ERA-2AEB202X | http://www.digikey.com/product-search/en?pv1=380&FV=fff40001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
R12 R51 R80 R109 R138 R167 R13 R52 R81 R110 R139 R168 R16 R55 R84 R113 R142 R17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 | 249K | 24 | R0402 | 1E-3 | ERJ-2RKF2493X | http://www.digikey.com/product-search/en?pv1=339&FV=fff40001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
R14 R53 R82 R111 R140 R169 | 100 | 6 | R0402 | 1E-3 | MCS0402MD1000BE100 | http://www.digikey.com/product-search/en?pv2=2&FV=fff40001%2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
R15 R54 R83 R112 R141 R170 | 2.49K | 6 | R0402 | 1E-3 | ERA-2AEB2491X | http://www.digikey.com/product-search/en?pv1=268&FV=fff40001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
R18 R57 R86 R115 R144 R173 | 27K | 6 | R0402 | 1E-3 | ERA-2AEB273X | http://www.digikey.com/product-detail/en/ERA-2AEB273X/P27KDC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
R187 R202 R204 R206 R208 R210 R212 | 30.1K | 7 | R0402 | 1E-3 | ERA-2AEB3012X | http://www.digikey.com/product-search/en?pv1=411&FV=fff40001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
R188 | 40.2K | 1 | R0402 | 1E-3 | ERA-2AEB4022X | http://www.digikey.com/product-search/en?pv1=503&FV=fff40001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
R2 R48 R105 R162 R219 R228 R6 R70 R106 R163 R220 R229 | 261 | 12 | R0402 | 1E-3 | ERA-2AEB2610X | http://www.digikey.com/product-detail/en/ERA-2AEB2610X/P261D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
R201 R203 R205 R207 R209 R211 | 51.1K | 6 | R0402 | 1E-3 | ERA-2AEB5112X | http://www.digikey.com/product-search/en?pv7=2&k=ERA-2AEB511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
R21 R60 R89 R118 R147 R176 R26 R65 R94 R123 R152 R181 R9 R76 R133 R214 R223 R232 | 3.32K | 18 | R0402 | 1E-3 | ERA-2AEB3321X | http://www.digikey.com/product-detail/en/ERA-2AEB3321X/P3.32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
R22 R185 | 5.0999999999999997E-2 | 2 | R0603 | 0.01 | UCR03EVPFSR051 | http://www.digikey.com/product-search/en?pv2=4&FV=fff40001%2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
R23 R62 R91 R120 R149 R178 | 24.3K | 6 | R0402 | 1E-3 | ERA-2AEB2432X | http://www.digikey.com/product-detail/en/ERA-2AEB2432X/P24.3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
R25 R64 R93 R122 R151 R180 | 2.4K | 6 | R0402 | 1E-3 | ERA-2AEB242X | http://www.digikey.com/product-detail/en/ERA-2AEB242X/P2.4KD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
R27 R66 R95 R124 R153 R182 R7 R74 R128 R164 R221 R230 | 4.75K | 12 | R0402 | 1E-3 | ERA-2AEB4751X | http://www.digikey.com/product-search/en?pv1=496&FV=fff40001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
R29 R68 R97 R126 R155 R184 | 6.49K | 6 | R0402 | 1E-3 | ERA-2AEB6491X | http://www.digikey.com/product-detail/en/ERA-2AEB6491X/P6.49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
R30 R31 R32 R33 R34 R35 R36 R40 R41 R42 R43 R45 R46 R56 R59 R189 R191 R193 R195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 | 10K | 33 | R0402 | 1E-3 | ERA-2AEB103X | http://www.digikey.com/product-search/en?pv1=112&FV=fff40001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
R37 | 71.5K | 1 | R0402 | 1E-3 | ERA-2AEB7152X | http://www.digikey.com/product-search/en?pv1=681&FV=fff40001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
R38 | 330 | 1 | R0402 | 1E-3 | ERA-2AEB331X | http://www.digikey.com/product-detail/en/ERA-2AEB331X/P330DC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
R39 | 9.09K | 1 | R0402 | 0.01 | ERA-2AEB9091X | http://www.digikey.com/product-search/en?pv1=741&FV=fff40001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
R47 R96 R125 R161 R218 R236 | 47K | 6 | R0402 | 0.01 | ERJ-2RKF4702X | https://www.digikey.com/product-detail/en/ERJ-2RKF4702X/P47.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
R5 R44 R73 R102 R131 R160 | 4.99K | 6 | R0402 | 1E-3 | ERJ-2RKF4991X | https://www.digikey.com/product-detail/en/ERJ-2RKF4991X/P4.9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
R61 R71 R85 R92 R100 R114 | 205K | 6 | R0402 | 1E-3 | ERJ-2RKF2053X | http://www.digikey.com/product-search/en?pv1=294&FV=fff40001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
R63 R72 R88 R98 R101 R117 R69 R77 R90 R99 R103 R119 | DNP | 12 | R0402 | 1E-3 | DNP
R8 R75 R132 R213 R222 R231 | 1.54K | 6 | R0402 | 1E-3 | ERA-2AEB1541X | http://www.digikey.com/product-detail/en/ERA-2AEB1541X/P1.54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
TH1 | NTCS0603E3103FMT | 1 | R0603 |  | NTCS0603E3103FMT | http://www.digikey.com/product-detail/en/NTCS0603E3103FMT/BC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
U1 U8 U11 U14 U17 U20 | LTC4411 | 6 | TSOT23-5 |  | LTC4411ES5#TRMPBF | http://www.digikey.com/product-detail/en/LTC4411ES5%23TRMPBF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
U2 U9 U12 U15 U18 U21 | TL1451A | 6 | PW16 |  | TL1451ACPWR | http://www.digikey.com/product-detail/en/TL1451ACPWR/296-101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
U23 | INA195 | 1 | SOT23-5 |  | INA195AIDBVR | http://www.digikey.com/product-detail/en/INA195AIDBVR/296-26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
U3 U10 U13 U16 U19 U22 | LM6144A | 6 | SO14 |  | LM6144AIM/NOPB | http://www.digikey.com/product-detail/en/LM6144AIM%2FNOPB/LM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
U5 U7 | ADS7828 | 2 | PW16 |  | ADS7828E/250 | http://www.digikey.com/product-detail/en/ADS7828E%2F250/296-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

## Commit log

2016-09-03 Basic first update of MPPT description.
2016-09-03 Adding images of Rev 2 MPPT PCBA
2016-09-03 Added image to description
2016-09-03 added license file so github license picker would show up again
2016-09-03 Updated license.md
    Updated with hardware notice and additional comments for FaradayRF and AMSAT affiliation.
2016-09-03 Updated license.md with user mentions
    Let's see if this works...
2016-09-03 Updated overview section
    Added overview section
2016-09-03 Added initial hardware files and a few directories
2016-09-03 Adding initial MPPT design files and updated documentation. May need some more work to clean up but mostly there.
2016-09-04 Updated readme.md
    Included necessary information about project structure to navigate repository and understand the project.
2016-09-04 Updated README.md Again
    Added history portion
2016-09-04 Fixed Readme.md RIT Link
2016-09-04 Revert "Fixed Readme.md RIT Link"
    This reverts commit 6a12c39ef28ecad01aae06bca14254cc2f457497.
2016-09-04 Changed image names to better describe files
2016-09-04 Updated Readme.md Image Link
    I broke the image link with image file renaming so fixing it now.
2016-09-04 Updated Readme with team members
2016-09-04 Updated License.md Spelling
2016-09-04 Added technical overview link
    Added to the overview section to highlight the importance of the technical overview document.
2016-09-06 Updated PDF export of technical document to remove comments from output file
2016-10-17 Updated Launch Timeline
    Per Jerry's comments via email
2017-07-04 Formatting and Wording Updates
    Fixed header formatting and removed specific launch dates.
2021-11-08 Update README.md
    https://forum.kicad.info/t/warning-avoid-all-links-to-kicad-pcb-org-use-kicad-org/31521
